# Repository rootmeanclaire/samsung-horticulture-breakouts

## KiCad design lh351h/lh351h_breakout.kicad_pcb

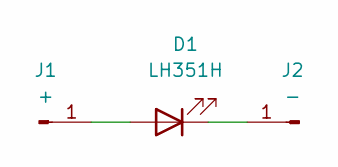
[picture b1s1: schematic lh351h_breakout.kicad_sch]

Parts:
D1: LH351H
J1: +; PinSocket_1x01_P2.54mm_Vertical
J2: -; PinSocket_1x01_P2.54mm_Vertical

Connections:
unnamed: D1.2 (A), J1.1
unnamed: D1.1 (K), J2.1

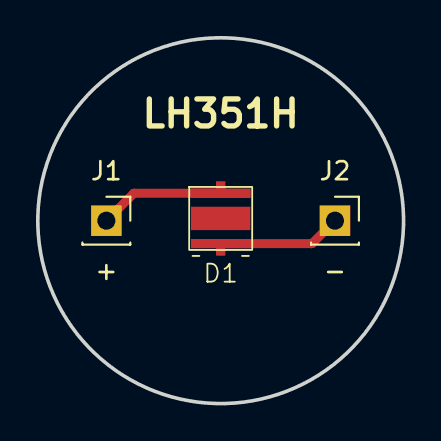
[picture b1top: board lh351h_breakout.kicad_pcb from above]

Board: 2 copper layers, 20.3 x 20.3 mm, 3 parts (0 on the bottom side), 2 nets.

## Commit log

2025-08-20 Added LH351H
2025-08-20 Add JLC PCB markings
2025-09-13 Fixed LH351H thermal pad
2025-09-13 Ignore fabrication outputs
